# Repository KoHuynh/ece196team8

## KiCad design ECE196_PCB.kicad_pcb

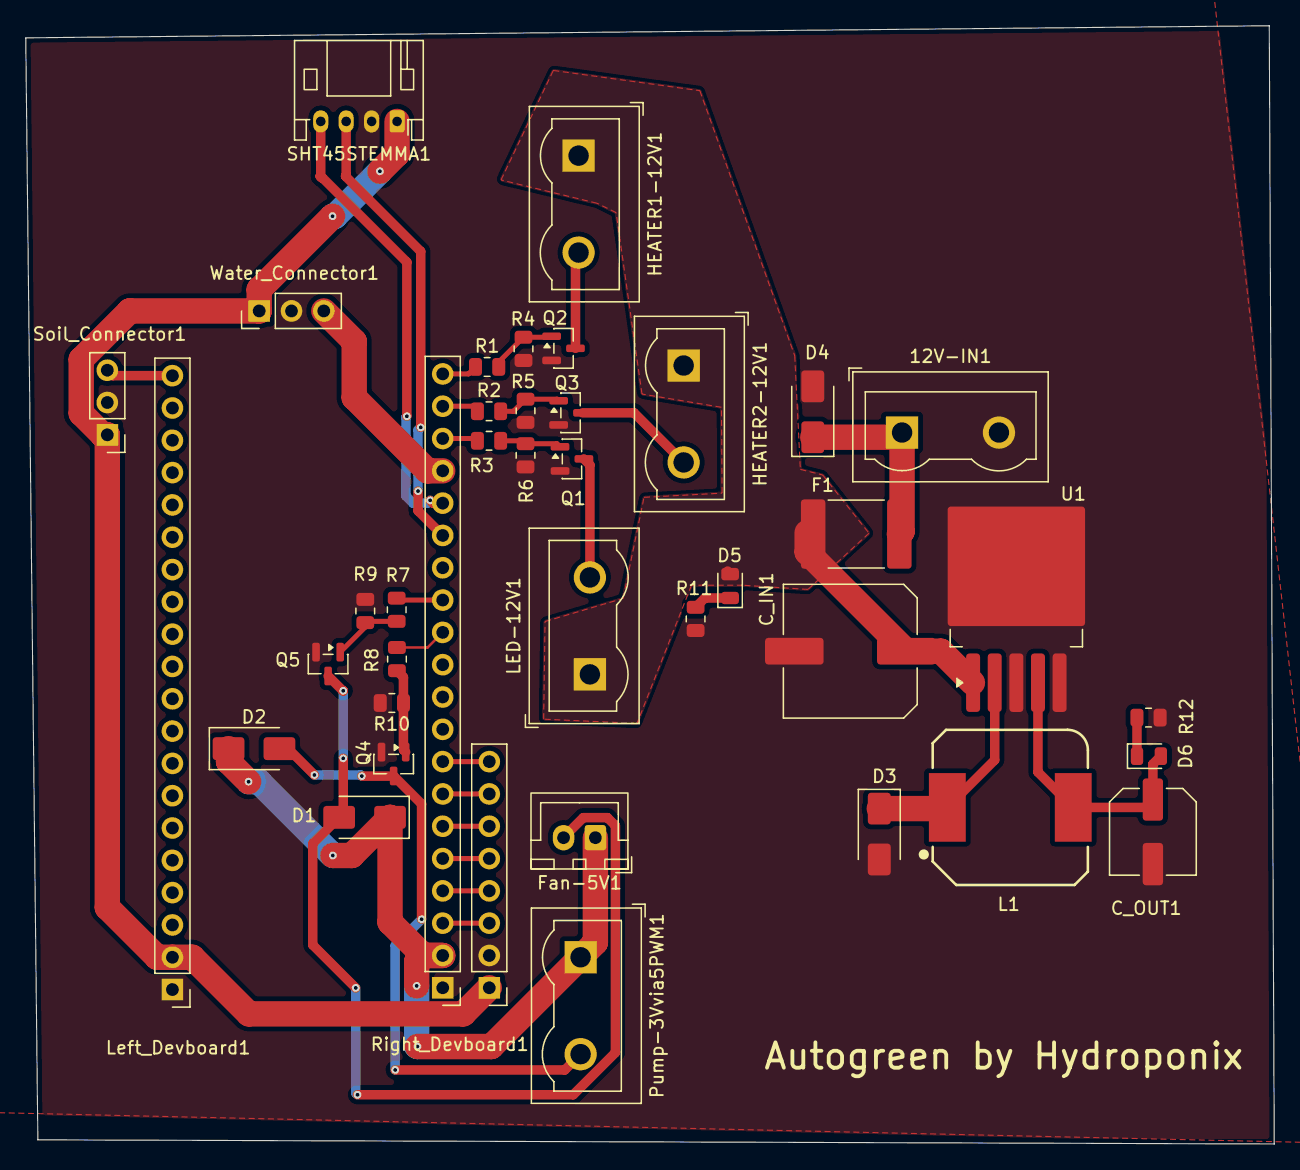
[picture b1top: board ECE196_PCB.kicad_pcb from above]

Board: 2 copper layers, 98.1 x 87.9 mm, 40 parts (0 on the bottom side), 34 nets.

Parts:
12V-IN1: Screw_Term; Wuerth_691311400102_P5.00mm
C_IN1: 680uF; C_Elec_10x10.2
C_OUT1: 220uF; C_Elec_6.3x7.7
D1, D2: SS14; D_SMA
D3: SS54; D_SMA
D4: SMAJ15A; D_SMA
D5: 12V; D_0805_2012Metric
D6: 5V; D_0805_2012Metric
Disp_Conn1: Conn_01x08; PinHeader_1x08_P2.54mm_Vertical
F1: Polyfuse; Fuse_2920_7451Metric
Fan-5V1: 1+2-; JST_XH_B2B-XH-A_1x02_P2.50mm_Vertical
HEATER1-12V1: Scr_Term2; Wuerth_691311400102_P5.00mm
HEATER2-12V1: Scr_Term3; Wuerth_691311400102_P5.00mm
L1: 33uH; L_Wurth_WE-PD_1260P
LED-12V1: Scr_Term1; Wuerth_691311400102_P5.00mm
Left_Devboard1: Conn_01x20; PinHeader_1x20_P2.54mm_Vertical
Pump-3Vvia5PWM1: 1+2-; Wuerth_691311400102_P5.00mm
Q1, Q2, Q3: AOSS32334C; SOT-23
Q4, Q5: BSS138; SOT-23
R1, R2, R3, R7, R8: 100; R_0805_2012Metric
R4, R5, R6, R9, R10: 10k; R_0805_2012Metric
R11: 1k; R_0805_2012Metric
R12: 330; R_0805_2012Metric
Right_Devboard1: Conn_01x20; PinHeader_1x20_P2.54mm_Vertical
SHT45STEMMA1: Conn_01x04; JST_PH_S4B-PH-K_1x04_P2.00mm_Horizontal
Soil_Connector1: Conn_01x03; PinHeader_1x03_P2.54mm_Vertical
U1: LM2596S-5; TO-263-5_TabPin3
Water_Connector1: Conn_01x03; PinHeader_1x03_P2.54mm_Vertical

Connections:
+3.3V: Disp_Conn1.1, Left_Devboard1.2, SHT45STEMMA1.1, Soil_Connector1.1, Water_Connector1.1
+5V: D1.1 (K), D2.1 (K), Fan-5V1.1, Pump-3Vvia5PWM1.1, Right_Devboard1.2
+12V_REG: C_IN1.1, D5.2 (A), F1.2, HEATER1-12V1.1, HEATER2-12V1.1, LED-12V1.1, U1.1 (VIN)
/BL: Disp_Conn1.8, Right_Devboard1.8
/CLK: Disp_Conn1.4, Right_Devboard1.4
/CS: Disp_Conn1.5, Right_Devboard1.5
/DC: Disp_Conn1.6, Right_Devboard1.6
/DISP_IN: Disp_Conn1.3, Right_Devboard1.3
/FANCONTROL: R7.1, Right_Devboard1.13
/FEEDBACK: C_OUT1.1, D6.2 (A), L1.2, U1.4 (FB)
/HEATER1PWM: R1.1, Right_Devboard1.20
/HEATER2PWM: R2.1, Right_Devboard1.19
/LEDPWM: R3.1, Right_Devboard1.18
/OUTPUT: D3.1 (K), L1.1, U1.2 (OUT)
/PUMPPWM: R8.1, Right_Devboard1.12
/RST: Disp_Conn1.7, Right_Devboard1.7
/SCL1: Right_Devboard1.15, SHT45STEMMA1.3
/SDA1: Right_Devboard1.16, SHT45STEMMA1.4
/SOIL_DAT: Left_Devboard1.20, Soil_Connector1.3
/WATER_DAT: Right_Devboard1.17, Water_Connector1.3
GND: 12V-IN1.2, C_IN1.2, C_OUT1.2, D3.2 (A), D4.2 (A2), Disp_Conn1.2, Left_Devboard1.1, Q1.2 (S), Q2.2 (S), Q3.2 (S), Q4.2 (S), Q5.2 (S), R4.2, R5.2, R6.2, R9.2, R10.2, R11.2, R12.2, Right_Devboard1.1, SHT45STEMMA1.2, Soil_Connector1.2, U1.3 (GND), U1.5 (~ON/OFF), Water_Connector1.2
unnamed: 12V-IN1.1, D4.1 (A1), F1.1
unnamed: D1.2 (A), Fan-5V1.2, Q5.3 (D)
unnamed: D2.2 (A), Pump-3Vvia5PWM1.2, Q4.3 (D)
unnamed: D5.1 (K), R11.1
unnamed: D6.1 (K), R12.1
unnamed: HEATER1-12V1.2, Q2.3 (D)
unnamed: HEATER2-12V1.2, Q3.3 (D)
unnamed: LED-12V1.2, Q1.3 (D)
unnamed: Q1.1 (G), R3.2, R6.1
unnamed: Q2.1 (G), R1.2, R4.1
unnamed: Q3.1 (G), R2.2, R5.1
unnamed: Q4.1 (G), R8.2, R10.1
unnamed: Q5.1 (G), R7.2, R9.1
